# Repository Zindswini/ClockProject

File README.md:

# ClockProject V2.0
This is the GitHub Companion to the Large scale RGB LED Clock as shown in [VIDEO IN PROGRESS]

# Design Files
- 3D and Circuit design was completed using Autodesk Fusion 360. Exports from the project are provided.
- Manufacturing was completed through JLC PCB, Gerber files exported from Fusion 360 are provided.

# Dependencies & Building
This project uses PlatformIO to manage dependencies. In theory, this should mean that you will not have to worry about dependencies and versioning. Just in case, a list of used libraries is provided below.

In order to program your own clock, you need to provide the appropriate credentials for your Wifi network. In order to connect, update the STASSID and STAPSK fields.

This project relies on:
### Libraries:
- [Adafruit ESP8266](https://github.com/adafruit/Adafruit_ESP8266) (In Library Browser)
- [Arduino JSON](https://github.com/bblanchon/ArduinoJson/tree/5.x)  (In Library Browser) (*Note version 5.x*)
- [DHTesp](https://github.com/beegee-tokyo/DHTesp) (In Library Browser)
- [NTPClient](https://github.com/arduino-libraries/NTPClient) (In Library Browser)
- [TelnetStream](https://github.com/jandrassy/TelnetStream) (In Library Browser)

### ESP Board
Add http://arduino.esp8266.com/stable/package_esp8266com_index.json to the "Additional Board Manager URLs" in the Arduino IDE, then add the esp8266 from inside the board manager.

Be sure to select "Adafruit Feather HUZZAH ESP8266" when compiling.

(this might be obsolete now that the project uses PlatformIO)

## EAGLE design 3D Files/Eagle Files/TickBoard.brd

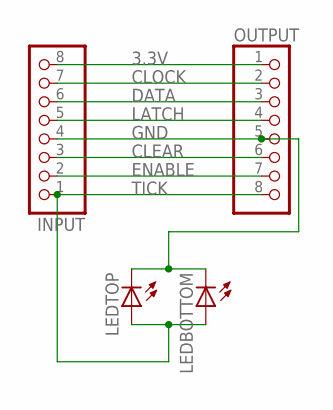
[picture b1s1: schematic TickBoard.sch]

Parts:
INPUT: PINHD-1X8/90; 1X08/90
LEDBOTTOM: LED5MM
LEDTOP: LED5MM
OUTPUT: PINHD-1X8/90; 1X08/90

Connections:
3.3V: INPUT.8, OUTPUT.1
CLEAR: INPUT.3, OUTPUT.6
CLOCK: INPUT.7, OUTPUT.2
DATA: INPUT.6, OUTPUT.3
ENABLE: INPUT.2, OUTPUT.7
GND: INPUT.4, LEDBOTTOM.K (C), LEDTOP.K (C), OUTPUT.5
LATCH: INPUT.5, OUTPUT.4
TICK: INPUT.1, LEDBOTTOM.A, LEDTOP.A, OUTPUT.8

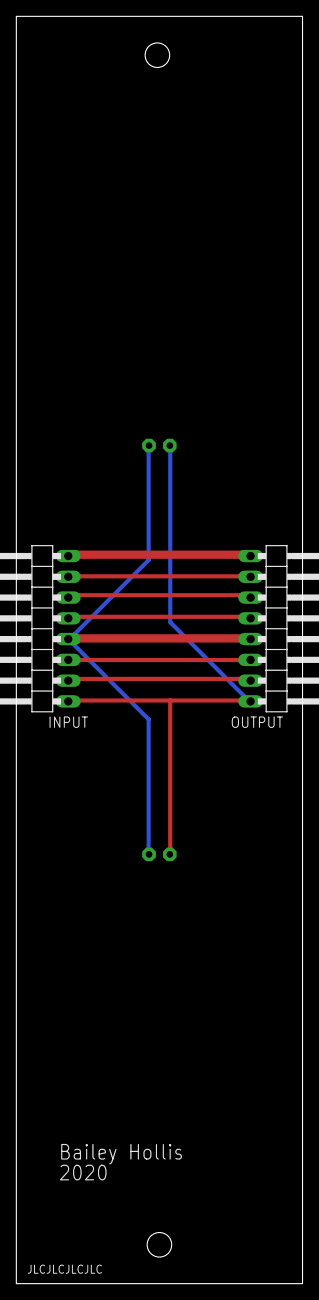
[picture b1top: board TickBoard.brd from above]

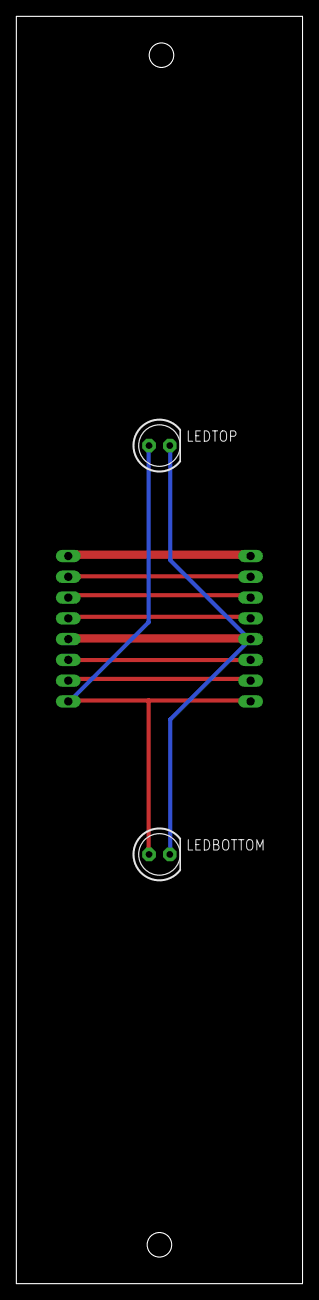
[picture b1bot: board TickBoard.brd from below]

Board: 2 copper layers, 35.0 x 155.0 mm, 4 parts (2 on the bottom side), 8 nets.

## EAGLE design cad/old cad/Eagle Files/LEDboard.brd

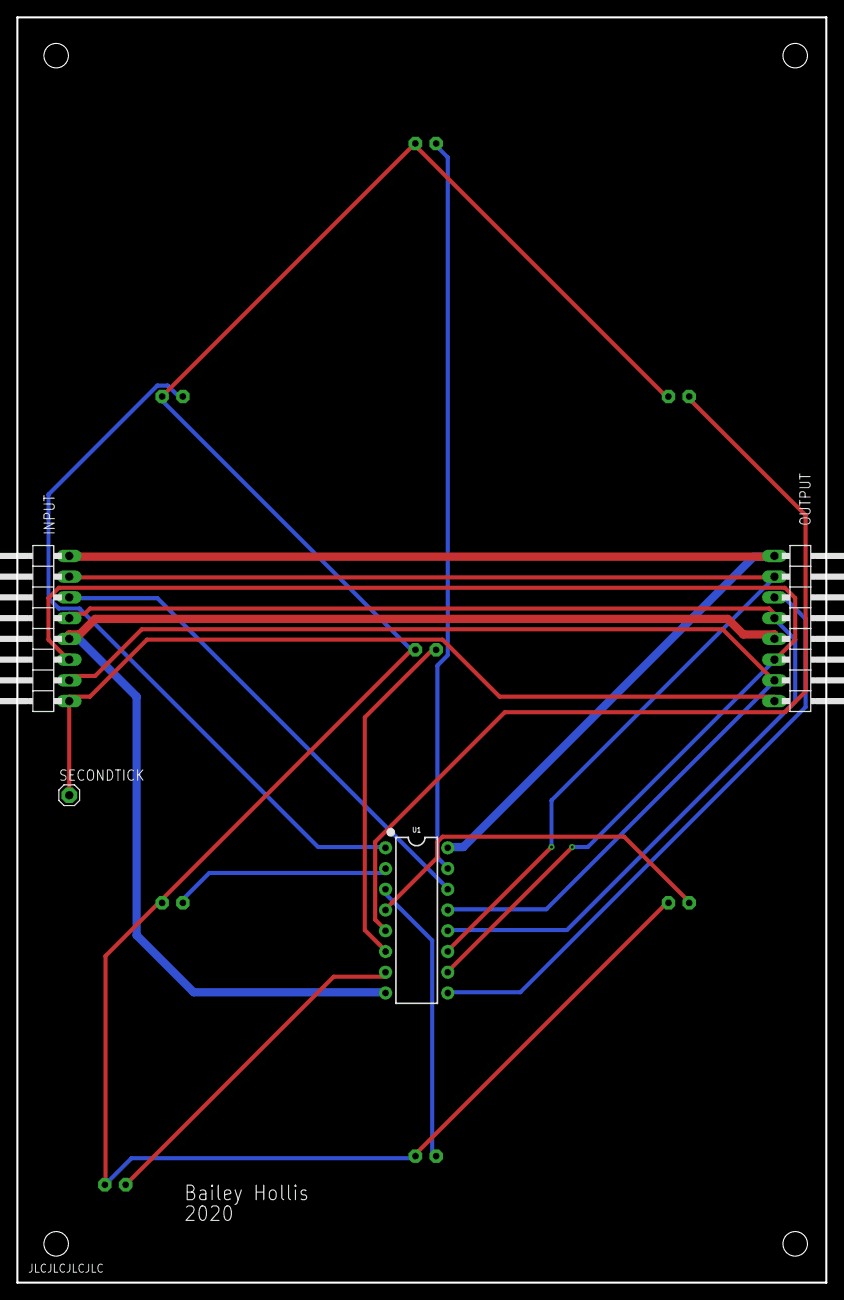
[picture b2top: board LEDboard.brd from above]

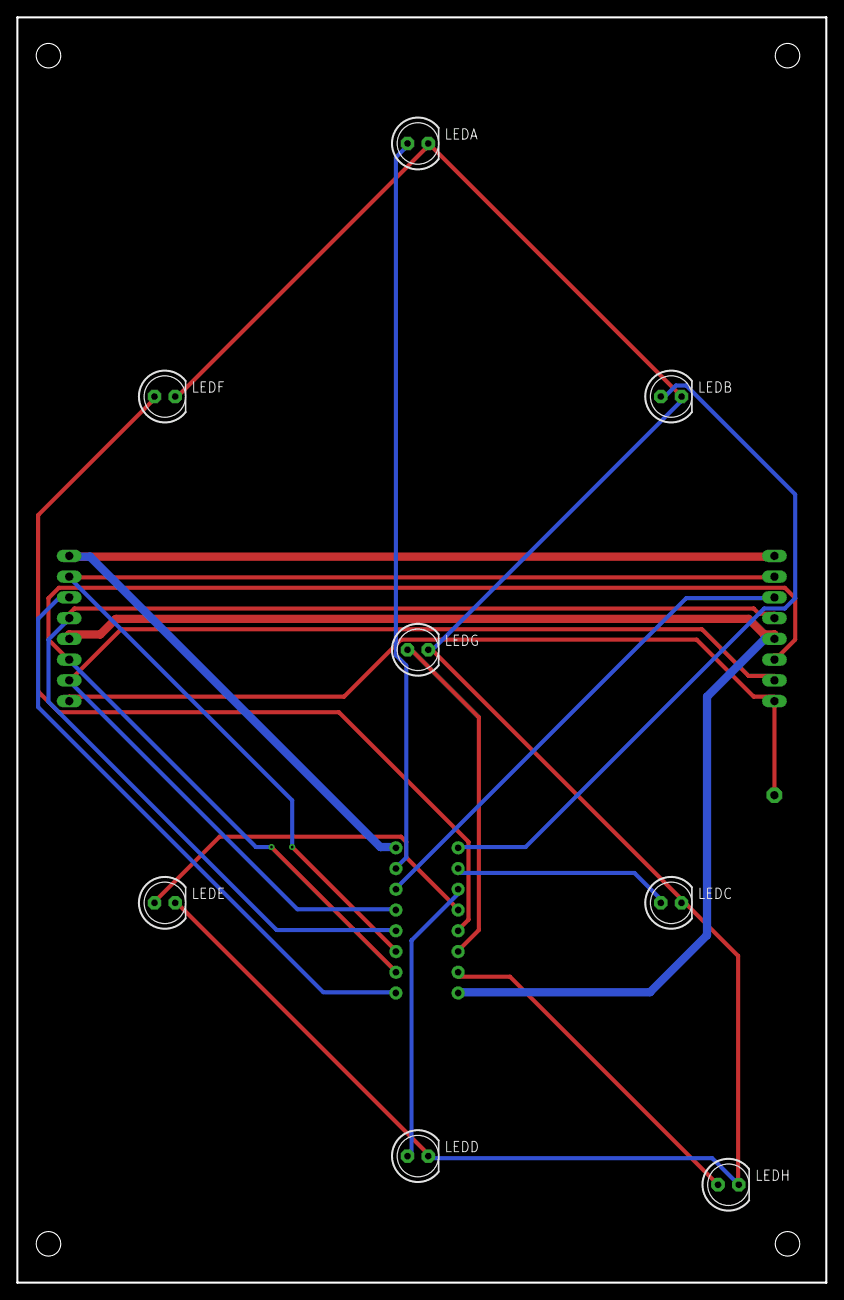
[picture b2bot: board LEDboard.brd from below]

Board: 2 copper layers, 99.1 x 154.9 mm, 12 parts (8 on the bottom side), 18 nets.

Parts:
INPUT: 1X08/90
LEDA: LED5MM
LEDB: LED5MM
LEDC: LED5MM
LEDD: LED5MM
LEDE: LED5MM
LEDF: LED5MM
LEDG: LED5MM
LEDH: LED5MM
OUTPUT: 1X08/90
SECONDTICK: 1X01
U1: SN74HC595N; DIP16

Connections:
CLEAR: INPUT.3, OUTPUT.6, U1.10
CLOCK: INPUT.7, OUTPUT.2, U1.11
DATAIN: INPUT.6, U1.14
DATAOUT: OUTPUT.3, U1.9
ENABLE: INPUT.2, OUTPUT.7, U1.13
GND: LEDA.K, LEDB.K, LEDC.K, LEDD.K, LEDE.K, LEDF.K, LEDG.K, LEDH.K
GROUND: INPUT.4, OUTPUT.5, U1.8
LATCH: INPUT.5, OUTPUT.4, U1.12
unnamed: LEDD.A, U1.3
unnamed: LEDA.A, U1.15
unnamed: LEDB.A, U1.1
unnamed: LEDC.A, U1.2
unnamed: LEDE.A, U1.4
unnamed: LEDF.A, U1.5
unnamed: LEDG.A, U1.6
unnamed: LEDH.A, U1.7
TICK: INPUT.1, OUTPUT.8, SECONDTICK.1
VCC: INPUT.8, OUTPUT.1, U1.16

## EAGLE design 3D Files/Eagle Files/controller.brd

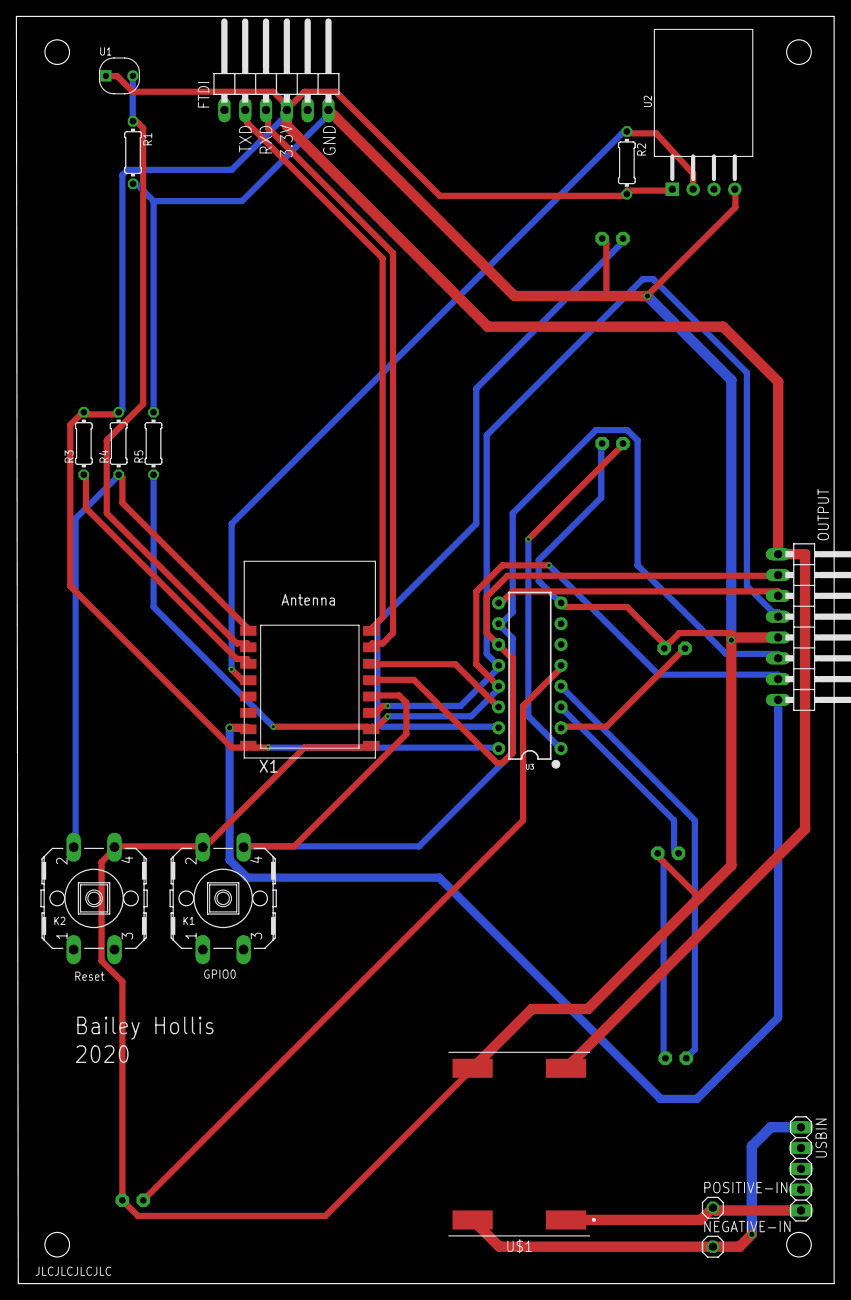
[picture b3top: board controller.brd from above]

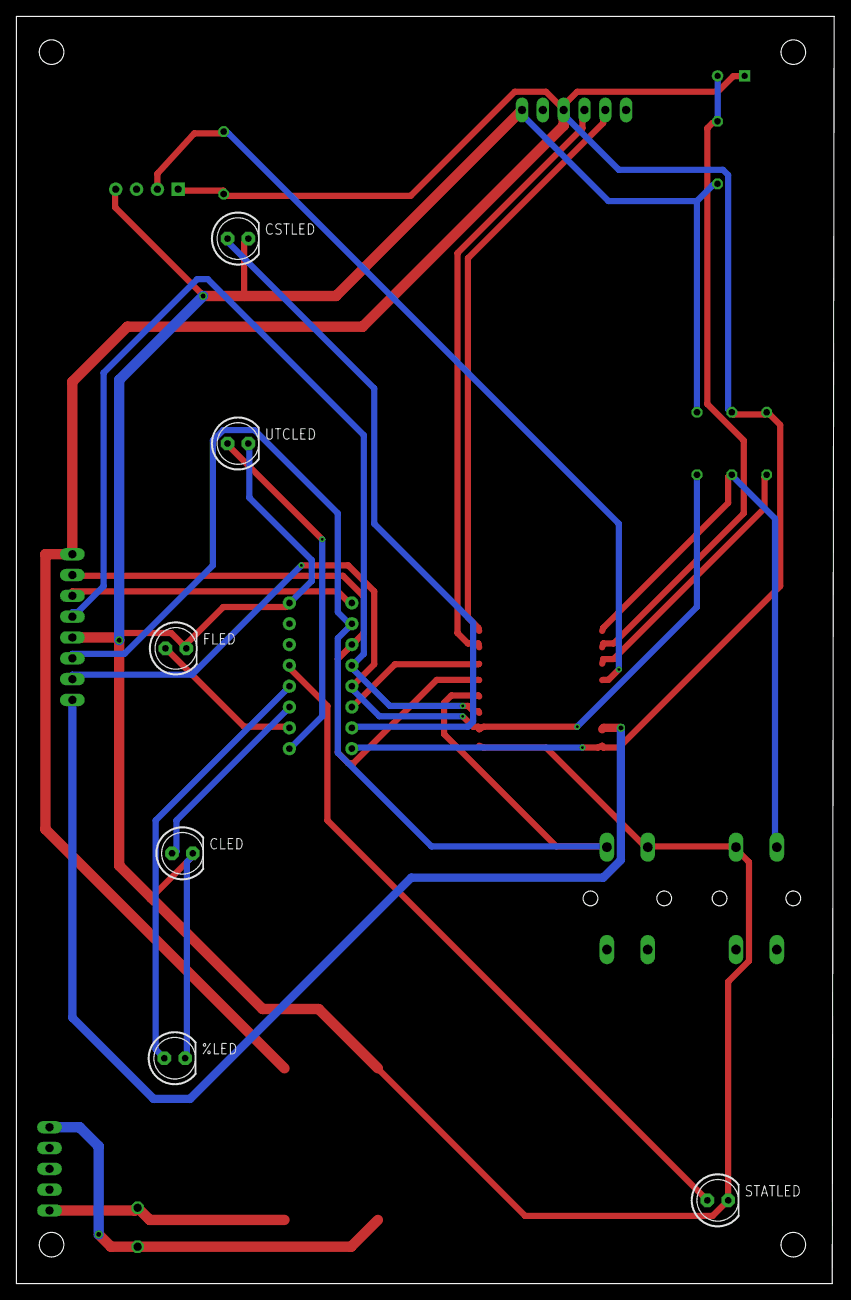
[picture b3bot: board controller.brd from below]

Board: 2 copper layers, 99.8 x 154.6 mm, 23 parts (6 on the bottom side), 23 nets.

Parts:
%LED: LED5MM
CLED: LED5MM
CSTLED: LED5MM
FLED: LED5MM
FTDI: 1X06/90
K1: GPIO 0; B3F-40XX
K2: Reset; B3F-40XX
NEGATIVE-IN: 1X01
OUTPUT: 1X08/90
POSITIVE-IN: 1X01
R1: 2.2k; 0204/7
R2: 10K; 0204/7
R3, R4, R5: 10k; 0204/7
STATLED: LED5MM
U1: PHOTORESISTOR; SNR2-3.0
U2: DHT11; SNR4-2.54-15.5X12.0X5.5MM
U3: SN74HC595N; DIP16
U$1: 3.3V OPTIMAL; DIODFN1720X2240X160-4N
USBIN: 1X05
UTCLED: LED5MM
X1: ESP-12

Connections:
+3V3: FTDI.4, OUTPUT.1, R2.2, R3.2, R4.1, U1.1, U2.1, U3.16, U$1.2, X1.8
CLEAR: K1.4, OUTPUT.6, U3.10, X1.12
CLOCK: OUTPUT.2, U3.11, X1.13
DATAIN: U3.14, X1.14
DATAOUT: OUTPUT.3, U3.9
ENABLE: OUTPUT.7, R5.1, U3.13, X1.10
GND: %LED.K, CLED.K, CSTLED.K, FLED.K, FTDI.6, K1.2, K2.4, OUTPUT.5, R1.2, R5.2, STATLED.K, U2.4, U3.8, U$1.3, UTCLED.K, X1.9
LATCH: OUTPUT.4, U3.12, X1.11
unnamed: CSTLED.A, U3.15
unnamed: U3.1, UTCLED.A
unnamed: NEGATIVE-IN.1, U$1.4, USBIN.1
unnamed: POSITIVE-IN.1, U$1.1, USBIN.5
unnamed: R1.1, U1.2, X1.2
unnamed: FLED.A, U3.2
unnamed: CLED.A, U3.3
unnamed: %LED.A, U3.4
unnamed: STATLED.A, U3.5
unnamed: R3.1, X1.3
unnamed: R2.1, U2.2, X1.4
unnamed: FTDI.2, X1.16
unnamed: FTDI.3, X1.15
unnamed: K2.2, R4.2, X1.1
TICK: OUTPUT.8, X1.7

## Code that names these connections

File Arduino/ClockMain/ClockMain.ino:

#include <ArduinoJson.h>
#include <DHTesp.h>
#include <NTPClient.h>
#include <WiFiClientSecure.h>
#include "credentials.h"
#include "OTA.h"

//define I/O pins
#define DHT_PIN 16
#define LSESNSOR_PIN A0

#define DATAOUT 5
#define CLOCK 4
#define CLEAR 0
#define LATCH 2
#define ENABLE 15
#define TICK 13

//WORKING VARS
//init dht11 vars
double localHumidity;
double localTemperature;
double lastTemp;
DHTesp dht;

double outsideHumidity;
double outsideTemperature;

double timeOffset = 0.0;
int brightness;

//init wifi and ntp vars
WiFiUDP ntpUDP;
NTPClient timeClient(ntpUDP, "pool.ntp.org", utcOffsetInSeconds);

//init temp vars
int mode = 0;
bool switched = false;
bool fadeDir;

//init number definitions
byte numbs[12];

void setup() {
  pinMode(DATAOUT, OUTPUT);
  pinMode(CLOCK, OUTPUT);
  pinMode(CLEAR, OUTPUT);
  pinMode(LATCH, OUTPUT);
  //pinMode(TICK, OUTPUT);

  digitalWrite(CLEAR, HIGH);
  Serial.begin(115200);

  //Init services
  startWifi(); //takes a while
  timeClient.begin();
  timeClient.update();
  timeClient.setUpdateInterval(120);
  dht.setup(DHT_PIN, DHTesp::DHT11);

  //OTA
  ArduinoOTA.setHostname("Wall Clock");
  setupOTA();
  
  //Set initial register pins
  digitalWrite(CLEAR, HIGH);
  digitalWrite(ENABLE, LOW);

  //define Numbers
  numbs[0] =   0xFC;
  numbs[1] =   0x60;
  numbs[2] =   0xDA;
  numbs[3] =   0xF2;
  numbs[4] =   0x66;
  numbs[5] =   0xB6;
  numbs[6] =   0xBE;
  numbs[7] =   0xE0;
  numbs[8] =   0xFE;
  numbs[9] =   0xF6;
  numbs[10] =  0x51;
  numbs[11] = B00000000;
}

void loop() {
  //handle weather clock, brightness data updating
  
  /* //Handle mode switching
  if(timeClient.getSeconds() % timePer == 0)
  {
    if(switched == false){
      fade();
      switched = true;
    }
  }
  else if(switched == true) { switched = false; }
  */
  
  if(timeClient.getSeconds() % 30 == 0 && switched == false) 
  {
    downloadData();

    //update time and offset
    long startTime = millis();
    timeClient.update();
    timeOffset = (millis() - startTime) / 1000;
    
    localTemperature = dht.getTemperature();
    localTemperature = constrain(localTemperature,0,999);

    localHumidity = dht.getHumidity();
    localHumidity = constrain(localHumidity,0,999);
  }
  
  //update brightness and tick
  brightness = updateBrightness();
  
  analogWrite(ENABLE, 1024 - updateBrightness());
  
  if(timeClient.getSeconds() % 2 == 0 && brightness == 1024){analogWrite(TICK, brightness);}
  else { analogWrite(TICK, 0); } 

  ArduinoOTA.handle();

  //shift out main display
  shifterOut(timeClient.getHours(),timeClient.getMinutes(),timeClient.getSeconds(),mode);
  shiftMode(mode);
  pulse(LATCH);

  //handle Night vs Day framerate
  if(brightness < 1024){
    delay(1000);
  }
  else{
  delay(50);
  }

  }
void shifterOut(int hr, int mn, int sec, int mode)
{
  //clear,shiftChar, latch
  switch (mode)
  {
    case 0: //Local time
      //calculate time difference
      int locHr;
      locHr = hr + utcOffsetInHours;
      if(locHr < 0){ locHr += 24; }
      else if(locHr > 24) { locHr -= 24; }

      if(twelvehr && locHr > 12){ locHr -= 12; }
      
      //Shift hour, minute, second
      shiftNumber(locHr);
      shiftNumber(mn);
      shiftNumber(round(sec + timeOffset));
      //Serial.println(locHr);
      break;

    case 1: //UST time
      if(twelvehr && hr > 12){ hr -= 12; }
      
      shiftNumber(hr);
      shiftNumber(mn);
      shiftNumber(round(sec + timeOffset));
      break;

    case 2: //Temp F
      shiftTemperature(round(convertToFahrenheit(localTemperature)),round(convertToFahrenheit(outsideTemperature)));
      break;

    case 3: //Temp C
      //shift outside temp
      shiftTemperature(round(localTemperature),round(outsideTemperature));
      break;

    case 4: //Humid %
      shiftTemperature(round(localHumidity),round(outsideHumidity));
      break;
  }
}

void startWifi()
{
  Serial.println();
  Serial.print("connecting to ");
  Serial.println(ssid);
  WiFi.mode(WIFI_STA);
  WiFi.begin(ssid, password);
  while (WiFi.status() != WL_CONNECTED) {
    delay(500);
    Serial.print(".");
  }
  Serial.println("");
  Serial.println("WiFi connected");
  Serial.println("IP address: ");
  Serial.println(WiFi.localIP());
}

void pulse(int pin)
{
  digitalWrite(pin, HIGH);
  digitalWrite(pin, LOW);
}

void dip(int pin)
{
  digitalWrite(pin, LOW);
  digitalWrite(pin, HIGH);
}

float convertToFahrenheit(float inTemp) { return inTemp * (9.00/5) + 32; }

String formatNumber(int in)
{
  if(in < 10) { return "0"+(String)in; }
  else { return (String)in; }
}

void shiftEmpty()
{
  digitalWrite(DATAOUT, LOW);
  for(int i = 0; i < 8; i++) { pulse(CLOCK); }
}

//Two digits max (duh)
void shiftNumber(int num)
{
  if(num < 10){
        shiftOut(DATAOUT,CLOCK, LSBFIRST,numbs[0]);
        shiftOut(DATAOUT,CLOCK, LSBFIRST,numbs[num]);
      }
      else{
        shiftOut(DATAOUT,CLOCK, LSBFIRST,numbs[num/10]);
        shiftOut(DATAOUT,CLOCK, LSBFIRST,numbs[num % 10]);
      }  
}

//properly handle single and triple digit temps
void shiftTemperature(int inTemp, int outTemp)
{
  inTemp = constrain(inTemp, 0, 999);
  outTemp = constrain(outTemp, 0, 999);
  
  if(outTemp <= 99) { shiftNumber(outTemp); shiftEmpty(); }
  else
  {
    shiftNumber(outTemp / 10);
    shiftOut(DATAOUT,CLOCK, LSBFIRST,numbs[outTemp % 10]);
  }
  
  if(inTemp <= 99) { shiftEmpty(); shiftNumber(inTemp);}
  else
  {
    shiftNumber(inTemp / 10);
    shiftOut(DATAOUT,CLOCK, LSBFIRST,numbs[inTemp % 10]);
  }
}

void shiftMode(int currentMode)
{
  digitalWrite(DATAOUT, HIGH);
  pulse(CLOCK);
  pulse(CLOCK);
  pulse(CLOCK);
  for(int i = 4; i >= 0; i--){
    if(currentMode == i)
    {
      digitalWrite(DATAOUT, HIGH);
    }
    else
    {
      digitalWrite(DATAOUT, LOW);
    }
    //digitalWrite(DATAOUT, HIGH);
    pulse(CLOCK);
  }
}

//thanks to RoboUlbricht on github for the demo code
void downloadData() {
  //connect to openweathermap
  WiFiClient client;
  Serial.print("connecting to ");
  Serial.println(host);
  if (!client.connect(host, 80)) {
    Serial.println("connection failed");
    return;
  }
  client.print(String("GET ") + param + " HTTP/1.1\r\n" +
               "Host: " + host + "\r\n" +
               "User-Agent: ESP8266\r\n" +
               "Connection: close\r\n\r\n");

  Serial.println("request sent");

  line = client.readStringUntil('\n');
  if (line != "HTTP/1.1 200 OK\r") {
    Serial.print("Unexpected response: ");
    Serial.println(line);
    return;
  }

  if (client.find("\r\n\r\n")) {
    DynamicJsonBuffer jsonBuffer(4096);
    JsonObject& root = jsonBuffer.parseObject(client);
    
    outsideTemperature = root["main"]["temp"];
    Serial.print("Temperature: ");
    Serial.println(outsideTemperature);

    outsideHumidity = root["main"]["humidity"];
    Serial.print("Humidity: ");
    Serial.println(outsideHumidity);
  } 
}

int updateBrightness()
{
  int count = 0;
  int value = 0;

  //attmept "denoising" by taking many readings
  for(int i = 0; i < 1000; i++){
  value += analogRead(A0);
  }
  value /= 1000;
  value /= 2;
  TelnetStream.println(value);
  if(value < lowAmbientBrightness){ value = 1; }
  else { value = 512; }
  

  value *= 2;
  return value;
}

//fade out, update screen, fade in. 512 resolution due to small decimals.
void fade()
{
  if(brightness < 1024)
  {
    //change mode
    changeMode();
  
    shifterOut(timeClient.getHours(),timeClient.getMinutes(),timeClient.getSeconds(),mode);
    shiftMode(mode);
    shifterOut(timeClient.getHours(),timeClient.getMinutes(),timeClient.getSeconds(),mode);
    shiftMode(mode);
    shifterOut(timeClient.getHours(),timeClient.getMinutes(),timeClient.getSeconds(),mode);
    shiftMode(mode);
    
    pulse(LATCH);
  }
  else{
  int fadebrightness = brightness / 2;
  //fade out
  while(fadebrightness > 0)
  {
    fadebrightness -= 1;
    analogWrite(ENABLE, 1024 - (fadebrightness * 2));
    delay(((fadeTime / 2) / brightness) * 10000);
    yield();
  }
  
  changeMode();
  
  //fade in
  while(fadebrightness < brightness / 2)
  {
    fadebrightness += 1;
    analogWrite(ENABLE, 1024 - (fadebrightness * 2));
    delay(((fadeTime / 2) / brightness) * 10000);
    yield();
  }
  }
  switched = false;
}

void changeMode()
{
  //change mode
  mode++;
  if(mode > 4) { mode=0; }

  //uncomment to disable UTC
  if(mode == 1) { mode++; }
  //uncomment to disable farenheit
  //if(mode == 2) { mode++; }
  //uncomment to disable celsius
  if(mode == 3) { mode++; }
  //uncomment to disable humidity
  if(mode == 4) { mode++; }
  
  if(mode > 4) { mode=0; }
  
  shifterOut(timeClient.getHours(),timeClient.getMinutes(),timeClient.getSeconds(),mode);
  shiftMode(mode);
  pulse(LATCH);
}

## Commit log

2020-07-26 Initial Files
2020-07-26 Add Pictures
2020-07-27 Images, Readme, Eagle files, Fusion files, STLs
2020-07-27 12hr support, fixed night modes
2021-01-26 Fix Spelling
2022-01-04 Fix images after branch rename
2022-01-04 Add PlatformIO Build
    Also moved functions around to make the C++ work
2022-05-26 Restructure files, init KiCad projects
2022-06-28 Initial work in Kicad and OpenSCAD
2022-07-14 Display CAD Progress
2023-10-15 Cleanup old file, test sync
2024-12-23 Add gitignore and pi pico KiCad submodule
2024-12-23 Initial work on importing necessary KiCad Libraries
2024-12-23 Add FreeCAD backup files to gitignore
2024-12-23 Initial Digit Schematic and Layout
2024-12-23 Initial Digit Component Placement
2024-12-27 Connected Controller Components, updated matrix footprint
2024-12-27 WIP Routing Controller
2024-12-27 Add some part+datasheet links to docs folder
2024-12-27 Remove .obsidian folder from git
2024-12-27 Add .obsidian to gitignore
2024-12-27 WIP Integrating USB C PD
2024-12-30 Move Power Circuit to sub schematic
2024-12-30 Finish schematic for PD Controller

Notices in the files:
parts and their libraries:
SparkFun-IC-Logic: Licensing: Creative Commons ShareAlike 4.0 International - https://creativecommons.org/licenses/by-sa/4.0
